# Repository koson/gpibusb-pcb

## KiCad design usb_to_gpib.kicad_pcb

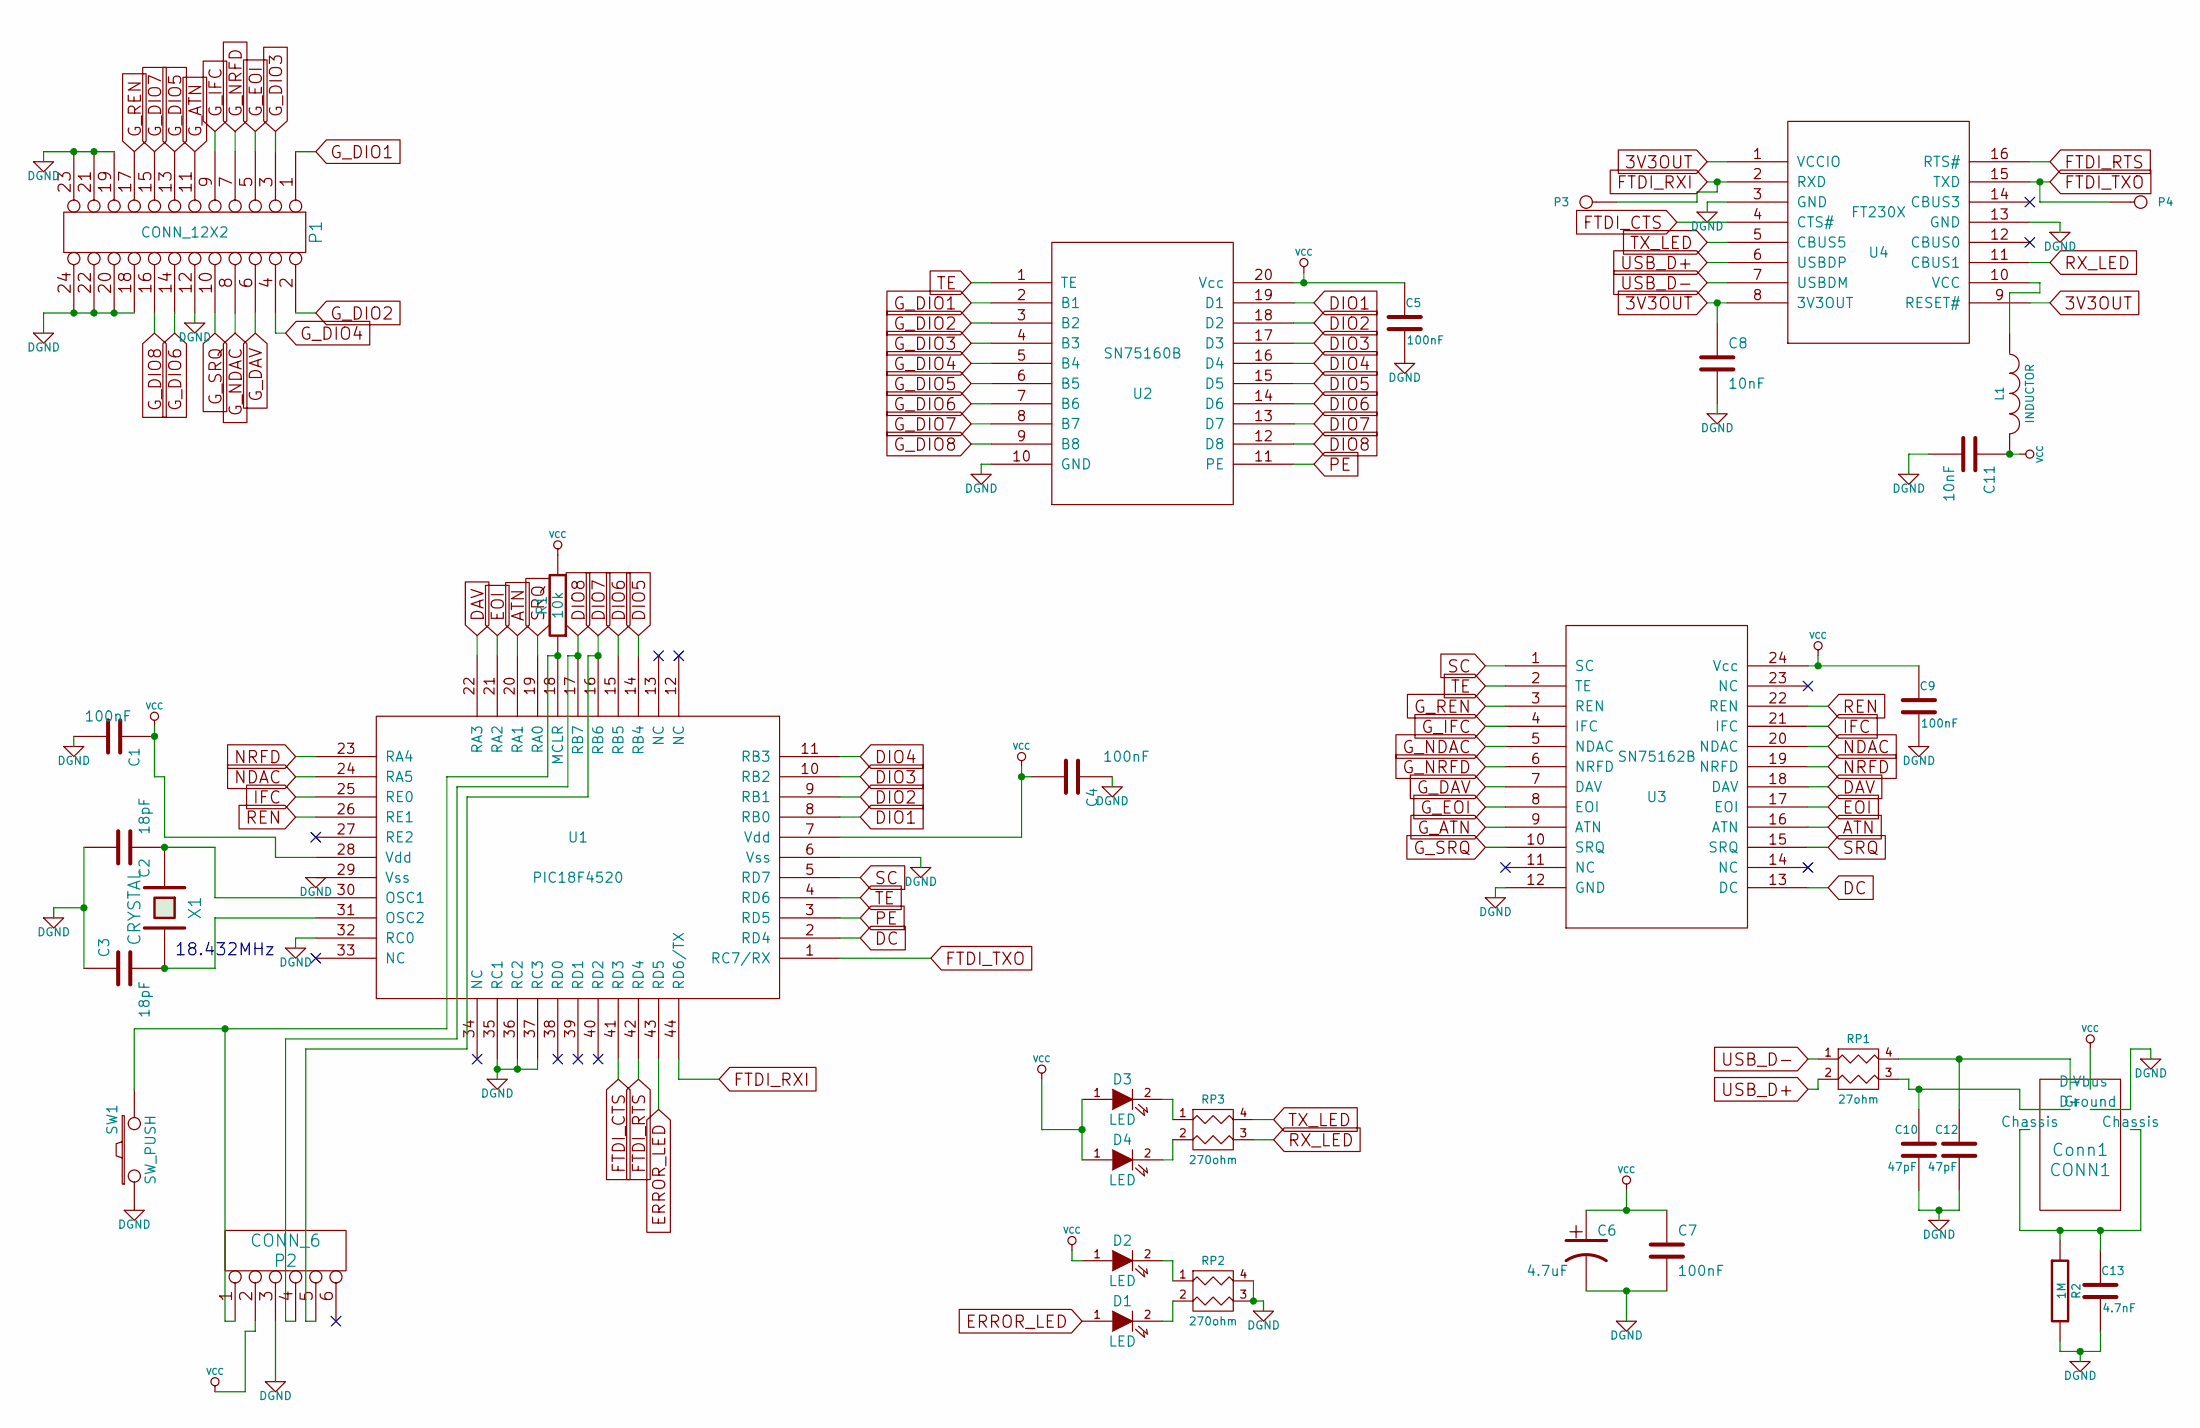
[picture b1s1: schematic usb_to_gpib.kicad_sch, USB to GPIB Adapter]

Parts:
C1, C4, C7: 100nF
C2, C3: 18pF
C5, C9: 100nF
C6: 4.7uF
C8, C11: 10nF
C10, C12: 47pF
C13: 4.7nF
CONN1: Conn1
D1, D2, D3, D4: LED
L1: INDUCTOR
P1: CONN_12X2
P2: CONN_6
P3, P4: CONN_1
R1: 10k
R2: 1M
RP1: 27ohm
RP2, RP3: 270ohm
SW1: SW_PUSH
U1: PIC18F4520
U2: SN75160B; MODULE
U3: SN75162B; MODULE
U4: FT230X; MODULE
X1: CRYSTAL

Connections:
3V3OUT: C8.1, U4.1 (VCCIO), U4.8 (3V3OUT), U4.9 (RESET#)
ATN: U1.20 (RA1), U3.16 (ATN)
DAV: U1.22 (RA3), U3.18 (DAV)
DC: U1.2 (RD4), U3.13 (DC)
DGND: C1.2, C2.2, C3.1, C4.1, C5.2, C6.2, C7.2, C8.2, C9.2, C10.2, C11.2, C12.2, C13.2, CONN1.4 (Ground), P1.12, P1.18, P1.19, P1.20, P1.21, P1.22, P1.23, P1.24, P2.3, R2.2, RP2.3 (R2), RP2.4 (R1), SW1.1, U1.6 (Vss), U1.29 (Vss), U1.32 (RC0), U1.35 (RC1), U1.36 (RC2), U1.37 (RC3), U2.10 (GND), U3.12 (GND), U4.3 (GND), U4.13 (GND)
DIO1: U1.8 (RB0), U2.19 (D1)
DIO2: U1.9 (RB1), U2.18 (D2)
DIO3: U1.10 (RB2), U2.17 (D3)
DIO4: U1.11 (RB3), U2.16 (D4)
DIO5: U1.14 (RB4), U2.15 (D5)
DIO6: U1.15 (RB5), U2.14 (D6)
DIO7: P2.5, U1.16 (RB6), U2.13 (D7)
DIO8: P2.4, U1.17 (RB7), U2.12 (D8)
EOI: U1.21 (RA2), U3.17 (EOI)
ERROR_LED: D1.1 (A), U1.43 (RD5)
FTDI_CTS: U1.41 (RD3), U4.4 (CTS#)
FTDI_RTS: U1.42 (RD4), U4.16 (RTS#)
FTDI_RXI: P3.1, U1.44 (RD6/TX), U4.2 (RXD); also elsewhere on the board
FTDI_TXO: P4.1, U1.1 (RC7/RX), U4.15 (TXD); also elsewhere on the board
G_ATN: P1.11, U3.9 (ATN)
G_DAV: P1.6, U3.7 (DAV)
G_DIO1: P1.1, U2.2 (B1)
G_DIO2: P1.2, U2.3 (B2)
G_DIO3: P1.3, U2.4 (B3)
G_DIO4: P1.4, U2.5 (B4)
G_DIO5: P1.13, U2.6 (B5)
G_DIO6: P1.14, U2.7 (B6)
G_DIO7: P1.15, U2.8 (B7)
G_DIO8: P1.16, U2.9 (B8)
G_EOI: P1.5, U3.8 (EOI)
G_IFC: P1.9, U3.4 (IFC)
G_NDAC: P1.8, U3.5 (NDAC)
G_NRFD: P1.7, U3.6 (NRFD)
G_REN: P1.17, U3.3 (REN)
G_SRQ: P1.10, U3.10 (SRQ)
IFC: U1.25 (RE0), U3.21 (IFC)
NDAC: U1.24 (RA5), U3.20 (NDAC)
NRFD: U1.23 (RA4), U3.19 (NRFD)
unnamed: C2.1, U1.30 (OSC1), X1.1
unnamed: C3.2, U1.31 (OSC2), X1.2
unnamed: C10.1, CONN1.3 (D+), RP1.3 (R2)
unnamed: C12.1, CONN1.2 (D-), RP1.4 (R1)
unnamed: C13.1, CONN1.5 (Chassis), CONN1.6 (Chassis), R2.1
unnamed: D1.2 (K), RP2.2
unnamed: D2.2 (K), RP2.1
unnamed: D3.2 (K), RP3.1
unnamed: D4.2 (K), RP3.2
unnamed: L1.1, U4.10 (VCC)
unnamed: P2.1, R1.1, SW1.2, U1.18 (MCLR)
PE: U1.3 (RD5), U2.11 (PE)
REN: U1.26 (RE1), U3.22 (REN)
RX_LED: RP3.3 (R2), U4.11 (CBUS1)
SC: U1.5 (RD7), U3.1 (SC)
SRQ: U1.19 (RA0), U3.15 (SRQ)
TE: U1.4 (RD6), U2.1 (TE), U3.2 (TE)
TX_LED: RP3.4 (R1), U4.5 (CBUS5)
USB_D+: RP1.2, U4.6 (USBDP)
USB_D-: RP1.1, U4.7 (USBDM)
VCC: C1.1, C4.2, C5.1, C6.1, C7.1, C9.1, C11.1, CONN1.1 (Vbus), D2.1 (A), D3.1 (A), D4.1 (A), L1.2, P2.2, R1.2, U1.7 (Vdd), U1.28 (Vdd), U2.20 (Vcc), U3.24 (Vcc)

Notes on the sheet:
18.432MHz

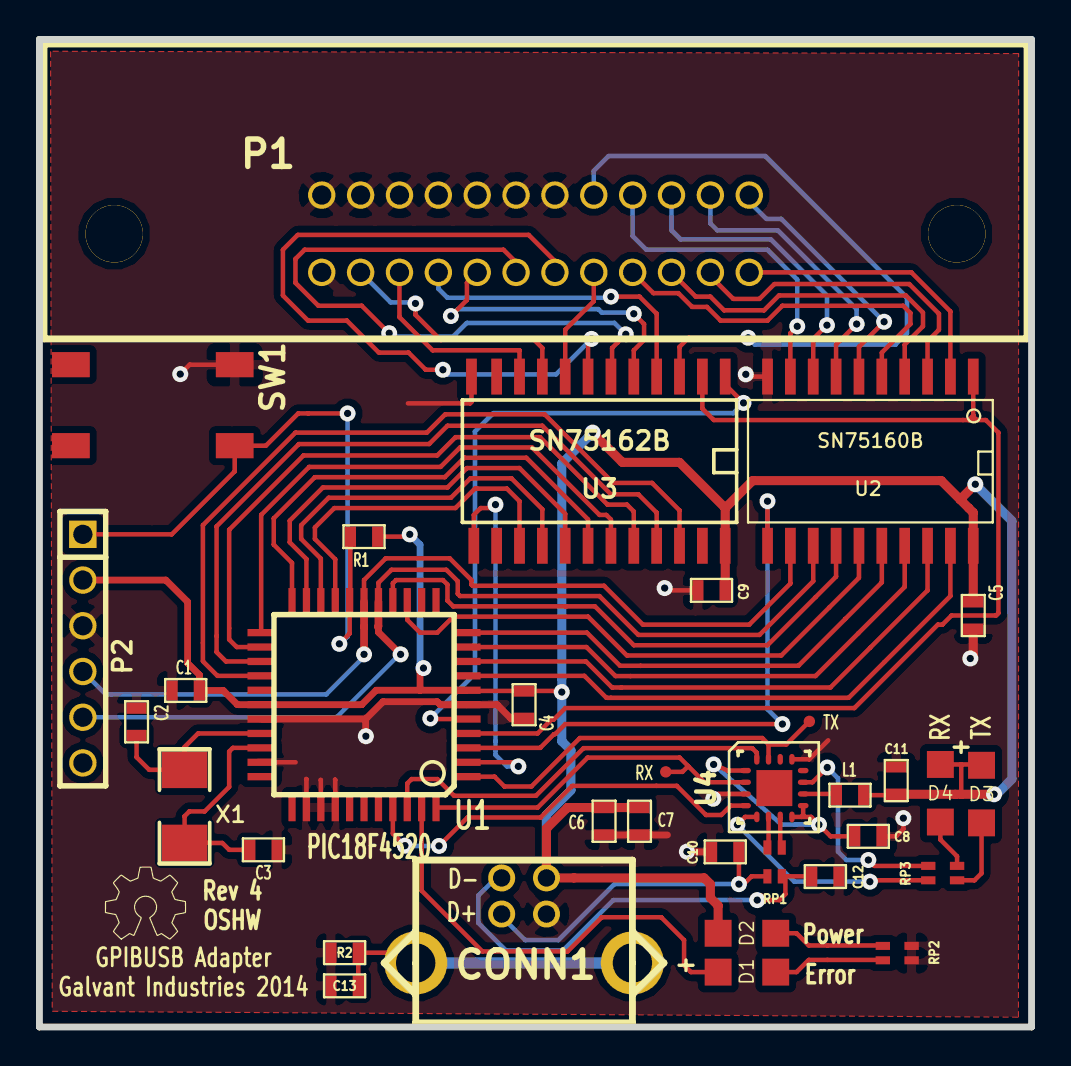
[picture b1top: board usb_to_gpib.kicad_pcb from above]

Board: 2 copper layers, 55.1 x 54.9 mm, 34 parts (0 on the bottom side), 59 nets.

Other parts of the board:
1PIN: P4; 1pin
1PIN#2: P3; 1pin

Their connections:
FTDI_RXI: 1PIN#2.1; also elsewhere on the board
FTDI_TXO: 1PIN.1; also elsewhere on the board

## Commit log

2021-05-31 upgrade to Kicad6

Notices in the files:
usb_to_gpib.kicad_pcb:
Released under Creative Commons
Attribution-ShareAlike 3.0 License
